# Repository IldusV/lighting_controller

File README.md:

# Lighting Controller Project

This project controls lights via Mqtt

## Preview

---

## Description

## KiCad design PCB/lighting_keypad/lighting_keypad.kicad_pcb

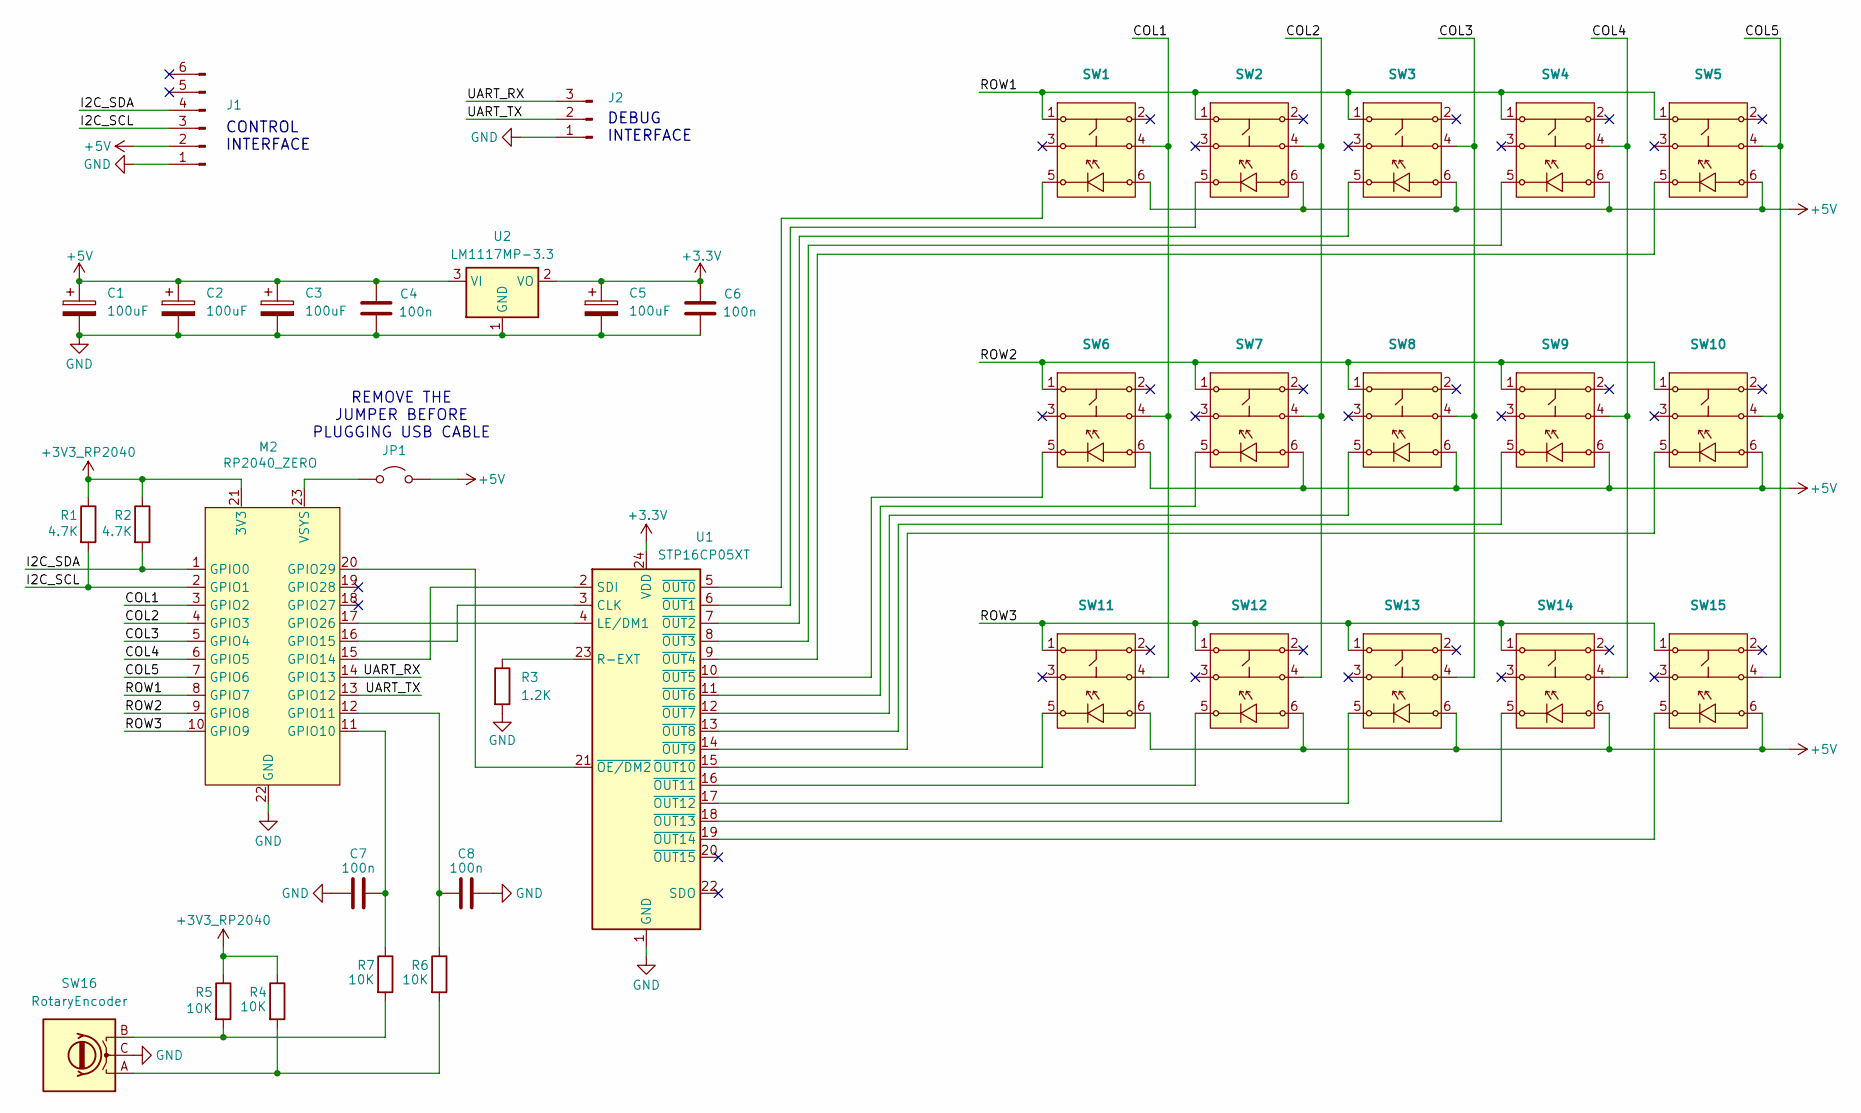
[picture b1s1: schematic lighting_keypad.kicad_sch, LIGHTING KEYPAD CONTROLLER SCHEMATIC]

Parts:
C1, C2, C3, C5: 100uF; CP_EIA-7343-30_AVX-N_Pad2.25x2.55mm_HandSolder
C4, C6, C7, C8: 100n; C_0603_1608Metric_Pad1.08x0.95mm_HandSolder
J1: Conn_01x06_Pin; PinHeader_1x06_P2.54mm_Vertical
J2: Conn_01x03_Pin; PinHeader_1x03_P2.54mm_Vertical
JP1: Jumper_2_Open; PinHeader_1x02_P2.54mm_Vertical
M2: RP2040_ZERO; RP2040-Zero
R1, R2: 4.7K; R_0603_1608Metric_Pad0.98x0.95mm_HandSolder
R3: 1.2K; R_0603_1608Metric_Pad0.98x0.95mm_HandSolder
R4, R5, R6, R7: 10K; R_0603_1608Metric_Pad0.98x0.95mm_HandSolder
SW1, SW2, SW3, SW4, SW5, SW6, SW7, SW8, SW9, SW10, SW11, SW12, SW13, SW14, SW15: Honyone_TS12
SW16: RotaryEncoder; RotaryEncoder_Alps_EC12E_Vertical_H20mm_CircularMountingHol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
U1: STP16CP05XT; SOIC127P1032X265-24N
U2: LM1117MP-3.3; SOT-223-3_TabPin2

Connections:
+3.3V: C5.1, C6.1, U1.24 (VDD), U2.2 (VO)
+3V3_RP2040: M2.21 (3V3), R1.1, R2.1, R4.1, R5.1
+5V: C1.1, C2.1, C3.1, C4.1, J1.2, JP1.2 (B), SW1.6, SW2.6, SW3.6, SW4.6, SW5.6, SW6.6, SW7.6, SW8.6, SW9.6, SW10.6, SW11.6, SW12.6, SW13.6, SW14.6, SW15.6, U2.3 (VI)
/COL1: M2.3 (GPIO2), SW1.4, SW6.4, SW11.4
/COL2: M2.4 (GPIO3), SW2.4, SW7.4, SW12.4
/COL3: M2.5 (GPIO4), SW3.4, SW8.4, SW13.4
/COL4: M2.6 (GPIO5), SW4.4, SW9.4, SW14.4
/COL5: M2.7 (GPIO6), SW5.4, SW10.4, SW15.4
/I2C_SCL: J1.3, M2.2 (GPIO1), R1.2
/I2C_SDA: J1.4, M2.1 (GPIO0), R2.2
/ROW1: M2.8 (GPIO7), SW1.1, SW2.1, SW3.1, SW4.1, SW5.1
/ROW2: M2.9 (GPIO8), SW6.1, SW7.1, SW8.1, SW9.1, SW10.1
/ROW3: M2.10 (GPIO9), SW11.1, SW12.1, SW13.1, SW14.1, SW15.1
/UART_RX: J2.3, M2.14 (GPIO13)
/UART_TX: J2.2, M2.13 (GPIO12)
GND: C1.2, C2.2, C3.2, C4.2, C5.2, C6.2, C7.2, C8.1, J1.1, J2.1, M2.22 (GND), R3.2, SW16.C, U1.1 (GND), U1.25 (GND), U2.1 (GND)
unnamed: JP1.1 (A), M2.23 (VSYS)
unnamed: C7.1, M2.11 (GPIO10), R7.1
unnamed: C8.2, M2.12 (GPIO11), R6.1
unnamed: M2.15 (GPIO14), U1.2 (SDI)
unnamed: M2.16 (GPIO15), U1.3 (CLK)
unnamed: M2.17 (GPIO26), U1.4 (LE/DM1)
unnamed: M2.20 (GPIO29), U1.21 (~OE/DM2)
unnamed: R4.2, R6.2, SW16.A
unnamed: R5.2, R7.2, SW16.B
unnamed: R3.1, U1.23 (R-EXT)
unnamed: SW1.5, U1.5 (~OUT0)
unnamed: SW2.5, U1.6 (~OUT1)
unnamed: SW3.5, U1.7 (~OUT2)
unnamed: SW4.5, U1.8 (~OUT3)
unnamed: SW5.5, U1.9 (~OUT4)
unnamed: SW6.5, U1.10 (~OUT5)
unnamed: SW7.5, U1.11 (~OUT6)
unnamed: SW8.5, U1.12 (~OUT7)
unnamed: SW9.5, U1.13 (~OUT8)
unnamed: SW10.5, U1.14 (~OUT9)
unnamed: SW11.5, U1.15 (~OUT10)
unnamed: SW12.5, U1.16 (~OUT11)
unnamed: SW13.5, U1.17 (~OUT12)
unnamed: SW14.5, U1.18 (~OUT13)
unnamed: SW15.5, U1.19 (~OUT14)

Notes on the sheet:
CONTROL INTERFACE
REMOVE THE JUMPER BEFORE PLUGGING USB CABLE
DEBUG INTERFACE

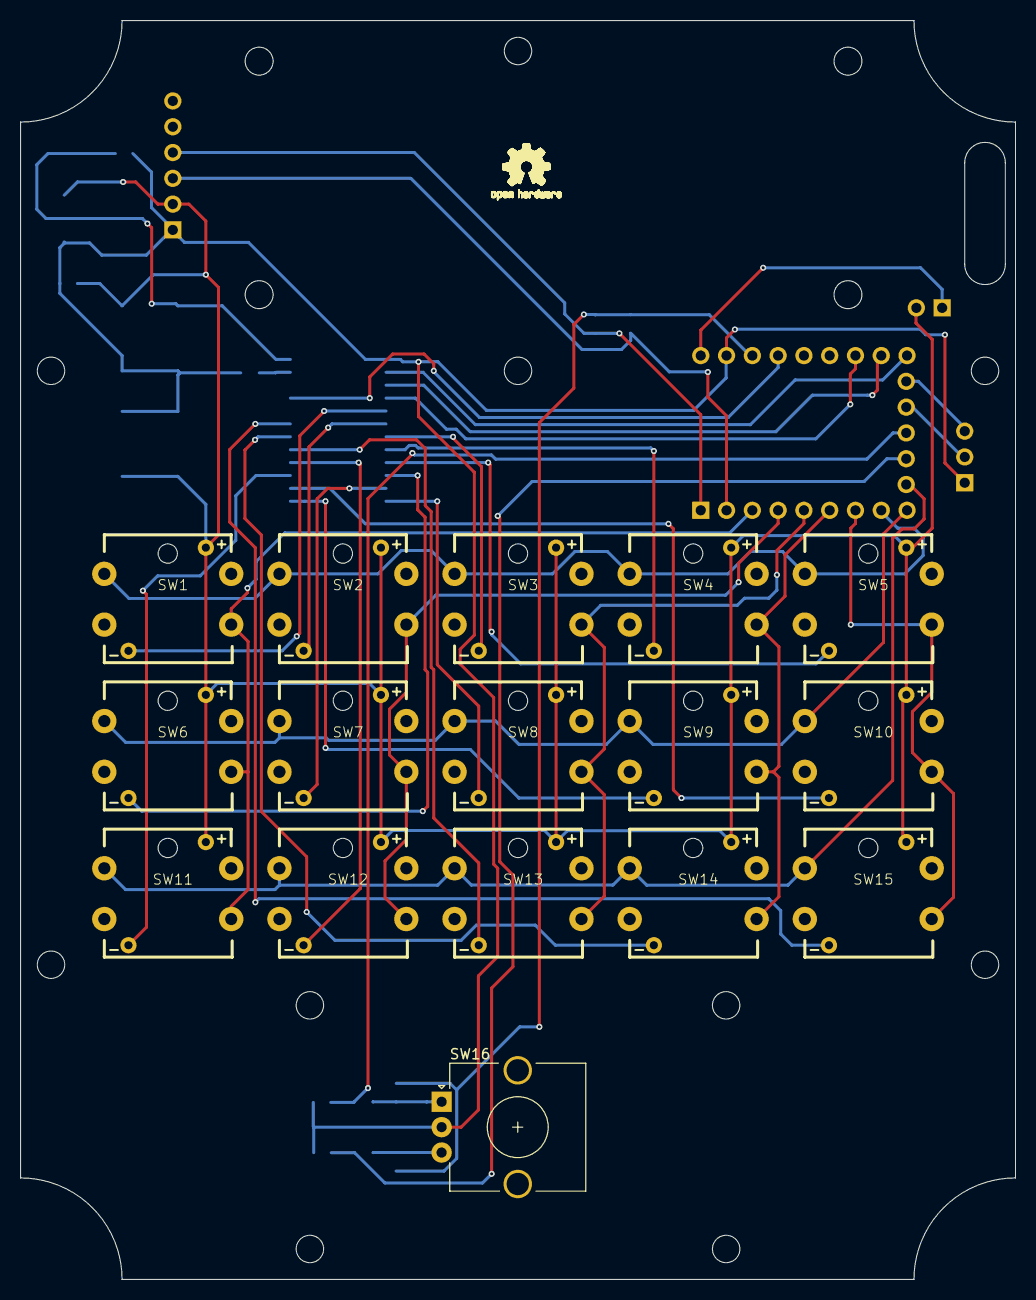
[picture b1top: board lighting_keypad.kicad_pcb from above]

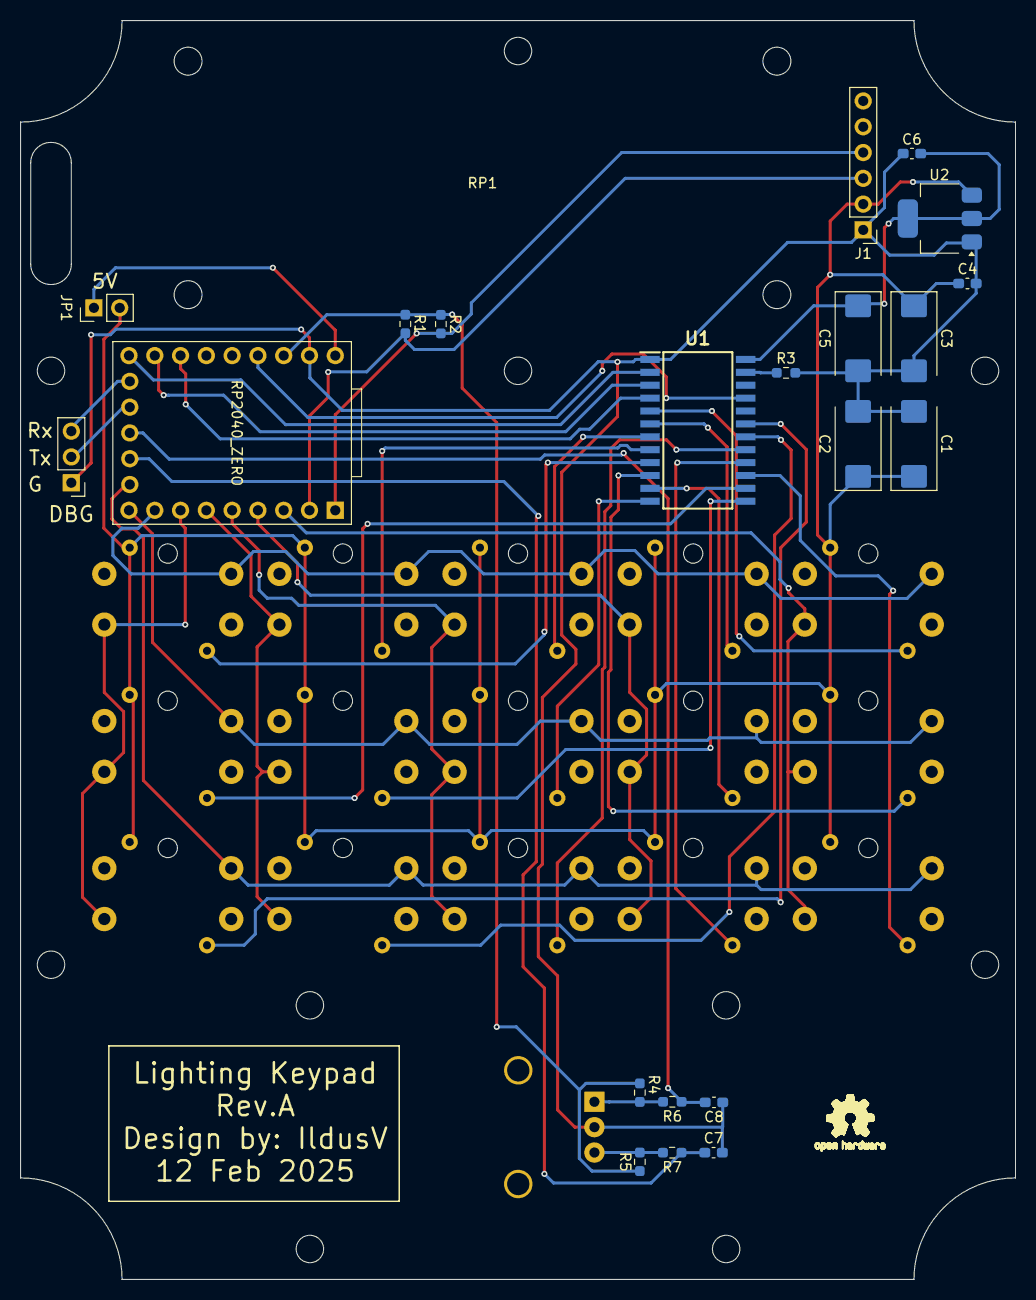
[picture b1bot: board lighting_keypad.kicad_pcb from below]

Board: 2 copper layers, 98.0 x 124.0 mm, 50 parts (23 on the bottom side), 41 nets.

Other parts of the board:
G1, G2: LOGO; OSHWLOGO0.3IN
MH1, MH2, MH3, MH4, MH5, MH6, MH7, MH8, MH9, MH10: MountingHole_2.7mm_M2.5
RP1: raspberry_pi_zero_outline

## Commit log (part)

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2025-02-23 Completed Rev.A
2026-02-06 Completed Rev.B
2026-02-07 Add u8g2 as submodule
2026-02-07 add raspi files
2026-02-07 Add keypad files
2026-02-07 Add remaining files
2026-02-08 rp2040 files
2026-02-14 added jlx25664 support via i2c
2026-02-18 modularized I2C & keypad driver
2026-03-08 Added: - Actuator status conatainer - Command manager to handle commands from keypad and status messages from MQTT - Event based handling
2026-03-08 added README.md
2026-03-22 Added U8G2Driver, DisplayRenderer, DisplayHandler
2026-03-27 Enhanced U8G2Driver to take i2c object, fixes #8
2026-03-29 Added WiFi connection state updates to main, fixes #22
2026-03-29 Added Mqtt SystemStatus updates and rendering, fixes #23
2026-03-30 Added queueing for mqtt messages, fixes #25
2026-04-02 Added queueing of the button events, fixes #24
2026-04-04 adjusted topics
2026-04-06 Implemented button LED handling, fixes #15
